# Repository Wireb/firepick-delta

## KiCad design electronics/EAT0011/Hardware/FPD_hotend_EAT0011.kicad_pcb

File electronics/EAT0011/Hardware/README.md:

### EAT0011 hot end and extruder module with I2C A2D

This hardware folder contains all the KiCad design files (logical and physical design) for the PCB. 

The gerber subdirectory has the final output files ready to be sent to a board house in standard gerber format. 

Also included in this directory is a PDF of the logics and 2 images of the front and back of the board in PNG format. 

Change list:

1. Updates for new micro.
1. Fixed silk screen for screw terminals.

TODO add info on on card programming.

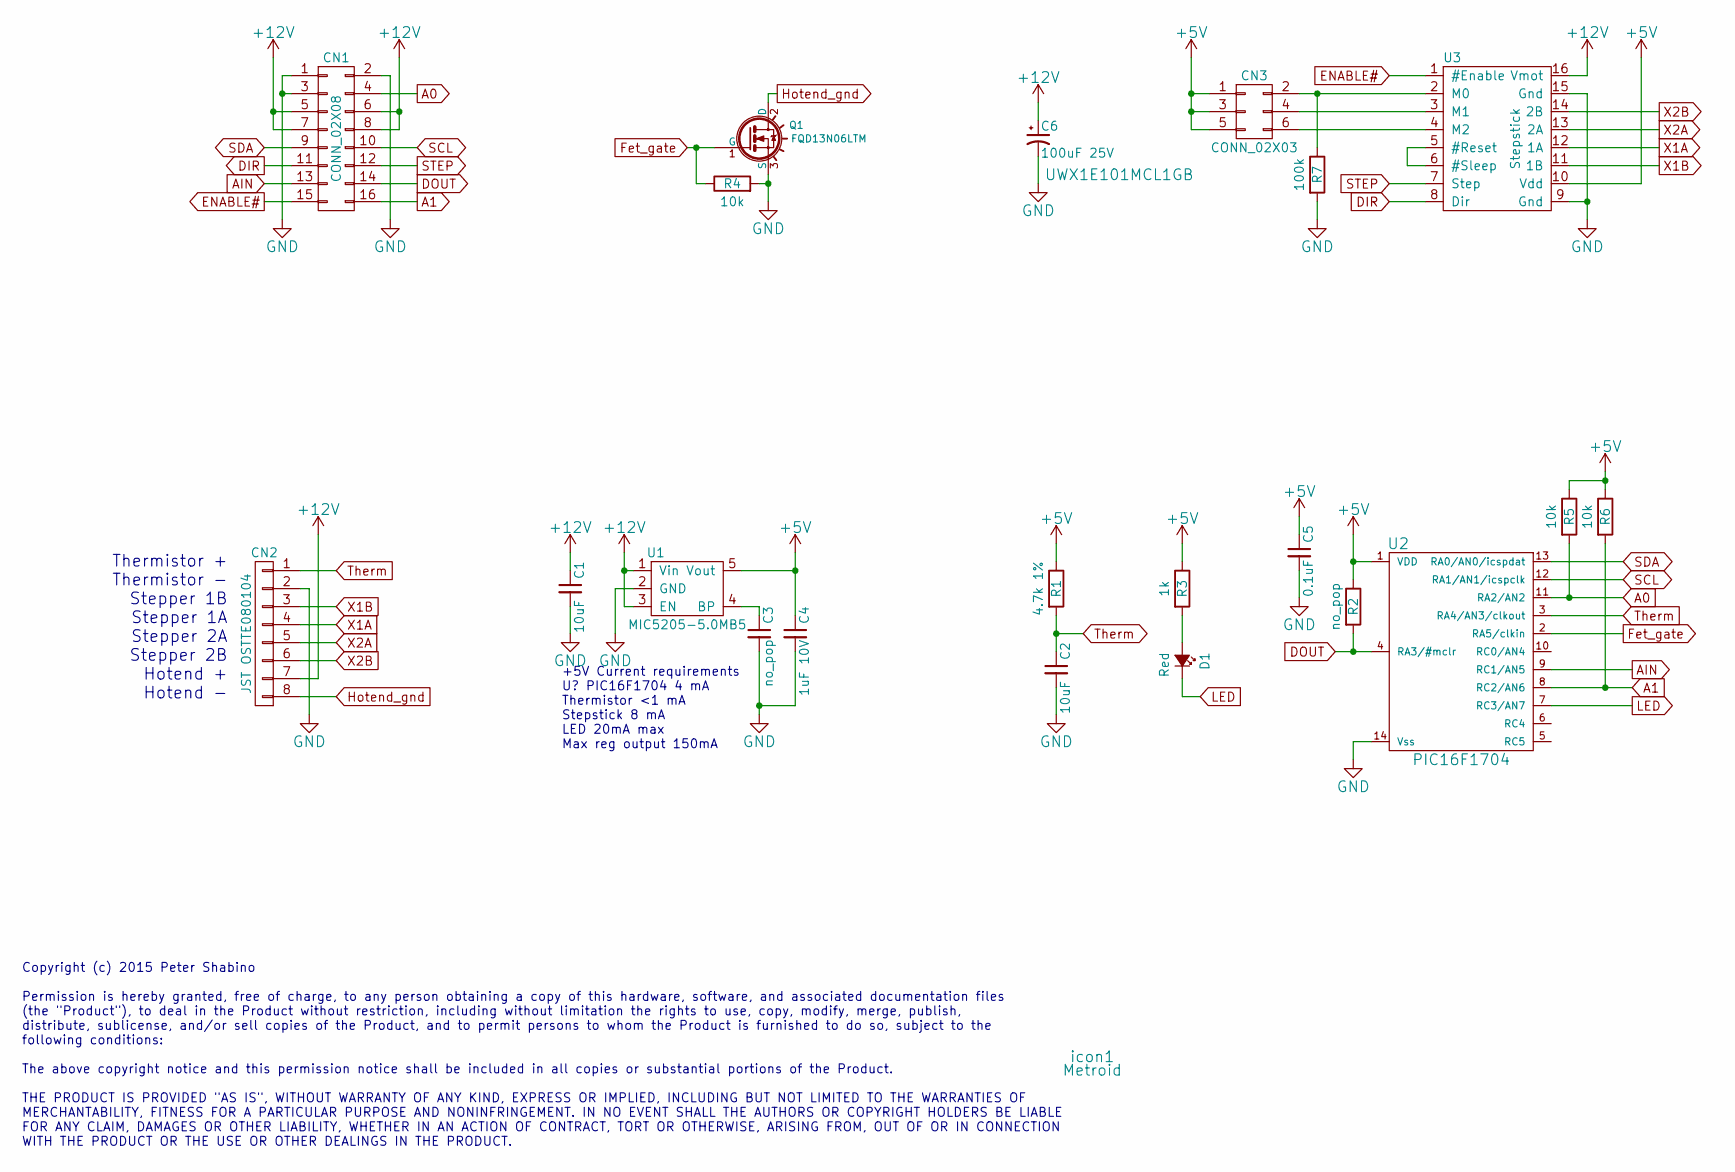
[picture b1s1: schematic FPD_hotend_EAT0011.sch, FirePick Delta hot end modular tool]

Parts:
C1, C2: 10uF; C_0805
C3: no_pop; C_0805
C4: 1uF 10V; C_0805
C5: 0.1uF; C_0805
C6: 100uF 25V; c_elec_6.3x7.7
CN1: CONN_02X08; 16pin_straddle_mount_100mil
CN2: JST OSTTE080104; OSTTE080104
CN3: CONN_02X03; Socket_Strip_Straight_2x03
D1: Red; LED-0805
Q1: FQD13N06LTM; D-Pak_TO252AA
R1: 4.7k 1%; C_0805
R2: no_pop; C_0805
R3: 1k; C_0805
R4, R5, R6: 10k; C_0805
R7: 100k; C_0805
U1: MIC5205-5.0MB5; SOT-23-5
U2: PIC16F1704; TSSOP-14_4.4x5mm_Pitch0.65mm
U3: Stepstick
icon1: Metroid; metroid

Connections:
+5V: C4.1, C5.1, CN3.1, CN3.3, CN3.5, R1.1, R2.1, R3.1, R5.1, R6.1, U1.5 (Vout), U2.1 (VDD), U3.10 (Vdd)
+12V: C1.1, C6.1, CN1.5, CN1.6, CN1.7, CN1.8, CN2.7, U1.1 (Vin), U1.3 (EN), U3.16 (Vmot)
A0: CN1.4, R5.2, U2.11 (RA2/AN2)
A1: CN1.16, R6.2, U2.8 (RC2/AN6)
AIN: CN1.13, U2.9 (RC1/AN5)
DIR: CN1.11, U3.8 (Dir)
DOUT: CN1.14, R2.2, U2.4 (RA3/#mclr)
ENABLE#: CN1.15, U3.1 (#Enable)
Fet_gate: Q1.1 (G), R4.1, U2.2 (RA5/clkin)
GND: C1.2, C2.2, C3.2, C4.2, C5.2, C6.2, CN1.1, CN1.2, CN1.3, CN2.2, Q1.3 (S), R4.2, R7.2, U1.2 (GND), U2.14 (Vss), U3.9 (Gnd), U3.15 (Gnd)
Hotend_gnd: CN2.8, Q1.2 (D)
LED: D1.2 (C), U2.7 (RC3/AN7)
unnamed: C3.1, U1.4 (BP)
unnamed: CN3.2, R7.1, U3.2 (M0)
unnamed: CN3.4, U3.3 (M1)
unnamed: CN3.6, U3.4 (M2)
unnamed: D1.1 (A), R3.2
unnamed: U3.5 (#Reset), U3.6 (#Sleep)
SCL: CN1.10, U2.12 (RA1/AN1/icspclk)
SDA: CN1.9, U2.13 (RA0/AN0/icspdat)
STEP: CN1.12, U3.7 (Step)
Therm: C2.1, CN2.1, R1.2, U2.3 (RA4/AN3/clkout)
X1A: CN2.4, U3.12 (1A)
X1B: CN2.3, U3.11 (1B)
X2A: CN2.5, U3.13 (2A)
X2B: CN2.6, U3.14 (2B)

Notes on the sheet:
Copyright (c) 2015 Peter Shabino Permission is hereby granted, free of charge, to any person obtaining a copy of this hardware, software, and associated documentation files (the "Product"), to deal in the Product without restriction, including without limitation the rights to use, copy, modify, mer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
+5V Current requirements U? PIC16F1704 4 mA Thermistor <1 mA Stepstick 8 mA LED 20mA max Max reg output 150mA
Thermistor + Thermistor - Stepper 1B Stepper 1A Stepper 2A Stepper 2B Hotend + Hotend -

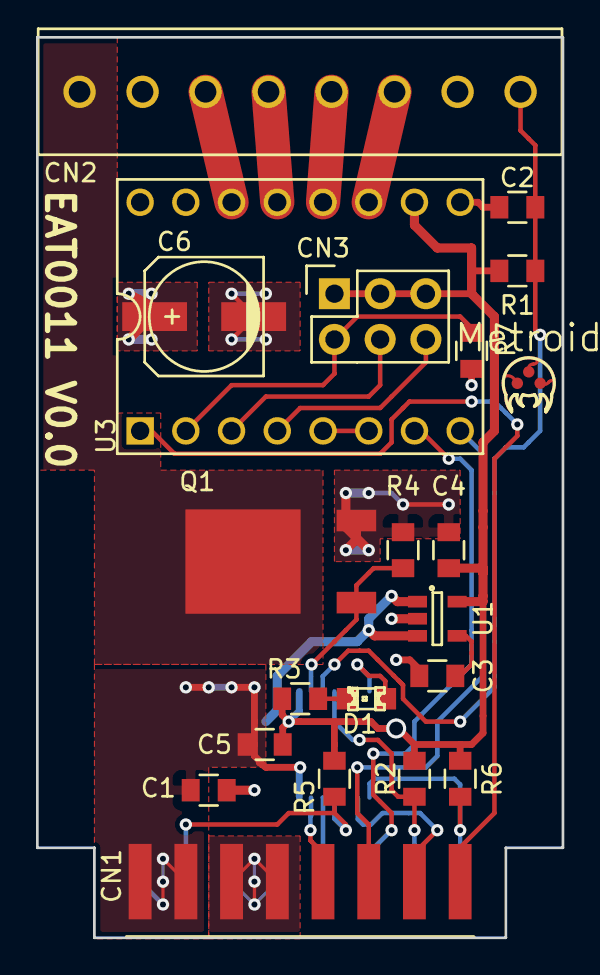
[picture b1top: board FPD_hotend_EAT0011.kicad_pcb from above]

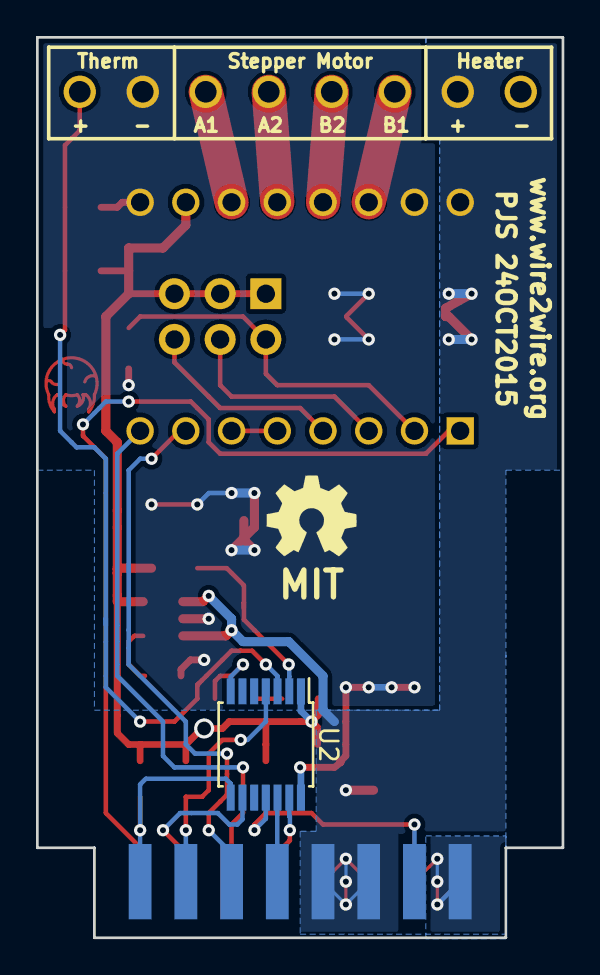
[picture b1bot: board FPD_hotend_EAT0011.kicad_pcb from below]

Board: 2 copper layers, 29.2 x 50.0 mm, 23 parts (2 on the bottom side), 26 nets.

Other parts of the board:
ICON***: OSH; OSH4mm

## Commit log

2015-10-06 EAT0010 rework instructions
    Docs for reworking a EAT0002 to a EAT0010.
2015-10-06 minor update
2015-10-07 Added EAT0011 rework instructions
2015-10-07 First pass of the EAT0010 board added
2015-10-07 minor update to EAT0010 hardware readme
2015-10-08 Added tool slot to I2C address table
2015-10-08 formatting fix
2015-10-08 PCB updates
    Added thermals and slid parts around a bit for better spacing
2015-10-11 Added BOM
    Added BOM and links to parts / PCBs
2015-10-17 EAT0011 started
    Logics done started PCB
2015-10-26 Fixed solder mask added EAT0011 files
    solder mask for the straddle mount header was both on the top layer
    instead of both layers. Finished the EAT0011 module data and BOM.
